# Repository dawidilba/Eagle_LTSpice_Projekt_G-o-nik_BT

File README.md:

## Eagle & LTSpice project - Przenosny głośnik bluetooth (schemat, wraz z symalacjami i PCB)

Projekt zrealizowany na przedmiot "Projektowanie Urządzeń Eletktronicznych" podczas 6 semestru studiów. W repozytorium znajdują się pliki źródłowe (wraz z potrzebnymi bibliotekami) do schematu i projektu płytki PCB (Program Eagle), a także symulacji (LTSpice). Dodatkowo zamieszczam szczegółową dokumentacje zrealizowanego projektu.

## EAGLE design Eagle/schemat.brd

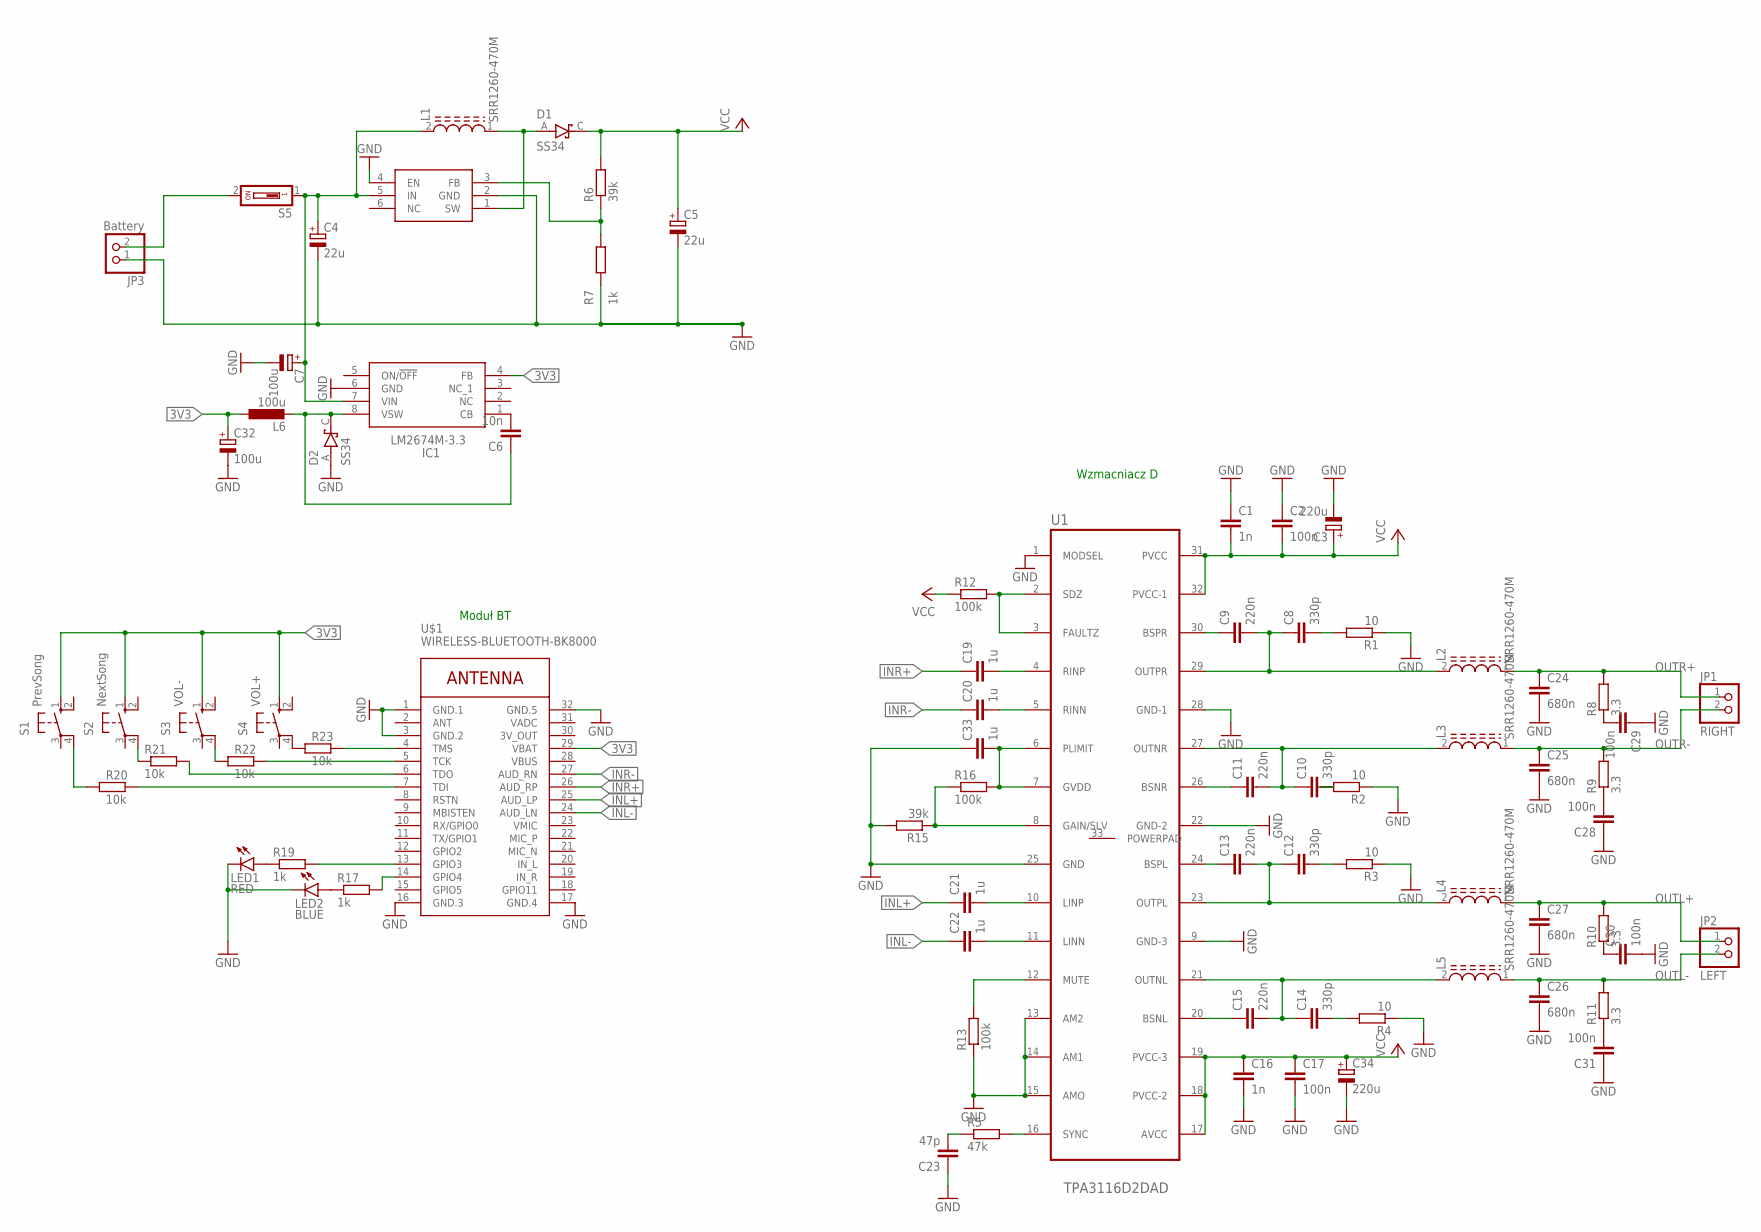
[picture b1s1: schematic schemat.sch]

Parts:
C1, C16: 1n; C0805
C2, C17, C28, C29, C30, C31: 100n; C0805
C3: 220u; 140CLH-0810
C4, C5: 22u; PANASONIC_D
C6: 10n; C0805
C7, C32: 100u; PANASONIC_D
C8, C10, C12, C14: 330p; C0805
C9, C11, C13, C15: 220n; C0805
C19, C20, C21, C22, C33: 1u; C0603
C23: 47p; C0603
C24, C25, C26, C27: 680n; C1206
C34: 220u; PANASONIC_D
D1, D2: SS34; DIOM7959X265N
IC1: LM2674M-3.3; SOIC127P600X175-8N
JP1: RIGHT; 1X02
JP2: LEFT; 1X02
JP3: Battery; 1X02
L1, L2, L3, L4, L5: SRR1260-470M; INDP125125X600N
L6: 100u; L1812
LED1: RED; CHIP-LED0805
LED2: BLUE; CHIP-LED0805
R1, R2, R3, R4: 10; R0805
R5: 47k; R0603
R6, R15: 39k; R0805
R7, R17, R19: 1k; R0805
R8, R9, R10, R11: 3.3; R0603
R12: 100k; R0603
R13, R16: 100k; R0805
R20, R21, R22, R23: 10k; R0805
S1: PrevSong; B3F-10XX
S2: NextSong; B3F-10XX
S3: VOL-; B3F-10XX
S4: VOL+; B3F-10XX
S5: DS01; DS-01
U1: TPA3116D2DAD; SOP65P810X120-33N
U2: MT3608; SOT95P280X145-6N
U$1: WIRELESS-BLUETOOTH-BK8000

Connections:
3V3: C32.+, IC1.4 (FB), L6.1, S1.1 (S), S2.1 (S), S3.1 (S), S4.1 (S), U$1.29 (VBAT)
3V_OUT: U$1.30 (3V_OUT)
BAT+: C4.+, C7.+, IC1.7 (VIN), L1.2, S5.1, U2.5 (IN)
BAT-: C4.-, C5.-, JP3.1, R7.1, U2.2 (GND)
GND: C1.1, C2.1, C3.-, C7.-, C16.2, C17.2, C23.1, C24.2, C25.2, C26.2, C27.2, C28.1, C29.1, C30.2, C31.1, C32.-, C33.1, C34.-, D2.A, IC1.6 (GND), LED1.C, LED2.C, R1.1, R2.1, R3.1, R4.1, R13.1, R15.2, U1.1 (MODSEL), U1.9 (GND-3), U1.13 (AM2), U1.14 (AM1), U1.15 (AMO), U1.22 (GND-2), U1.25 (GND), U1.28 (GND-1), U2.4 (EN), U$1.1 (GND.1), U$1.3 (GND.2), U$1.16 (GND.3), U$1.17 (GND.4), U$1.32 (GND.5)
INL+: C21.1, U$1.25 (AUD_LP)
INL-: C22.1, U$1.24 (AUD_LN)
INR+: C19.1, U$1.26 (AUD_RP)
INR-: C20.1, U$1.27 (AUD_RN)
unnamed: D1.A, L1.1, U2.1 (SW)
unnamed: C9.1, U1.30 (BSPR)
unnamed: C8.1, C9.2, L2.2, U1.29 (OUTPR)
unnamed: C12.1, C13.2, L4.2, U1.23 (OUTPL)
unnamed: C8.2, R1.2
unnamed: C11.1, U1.26 (BSNR)
unnamed: C10.1, C11.2, L3.2, U1.27 (OUTNR)
unnamed: C10.2, R2.2
unnamed: C13.1, U1.24 (BSPL)
unnamed: C15.1, U1.20 (BSNL)
unnamed: C12.2, R3.2
unnamed: C14.2, R4.2
unnamed: C6.1, D2.C (K), IC1.8 (VSW), L6.2
unnamed: R6.1, R7.2, U2.3 (FB)
unnamed: C19.2, U1.4 (RINP)
unnamed: C14.1, C15.2, L5.2, U1.21 (OUTNL)
unnamed: C20.2, U1.5 (RINN)
unnamed: C21.2, U1.10 (LINP)
unnamed: C22.2, U1.11 (LINN)
unnamed: C23.2, R5.1
unnamed: R5.2, U1.16 (SYNC)
unnamed: R22.1, S3.4 (P1)
unnamed: LED2.A, R17.1
unnamed: LED1.A, R19.1
unnamed: R17.2, U$1.14 (GPIO4)
unnamed: C28.2, R9.1
unnamed: C29.2, R8.1
unnamed: C30.1, R10.1
unnamed: C31.2, R11.1
unnamed: R12.2, U1.2 (SDZ), U1.3 (FAULTZ)
unnamed: R13.2, U1.12 (MUTE)
unnamed: C33.2, R16.2, U1.6 (PLIMIT), U1.7 (GVDD)
unnamed: R19.2, U$1.13 (GPIO3)
unnamed: R15.1, R16.1, U1.8 (GAIN/SLV)
unnamed: C6.2, IC1.1 (CB)
unnamed: R21.1, S2.4 (P1)
unnamed: R20.2, U$1.7 (TDI)
unnamed: R21.2, U$1.6 (TDO)
unnamed: R20.1, S1.4 (P1)
unnamed: R23.1, S4.4 (P1)
unnamed: JP3.2, S5.2
unnamed: R22.2, U$1.5 (TCK)
unnamed: R23.2, U$1.4 (TMS)
OUTL+: C27.1, JP2.1, L4.1, R10.2
OUTL-: C26.1, JP2.2, L5.1, R11.2
OUTR+: C24.1, JP1.1, L2.1, R8.2
OUTR-: C25.1, JP1.2, L3.1, R9.2
VADC: U$1.31 (VADC)
VCC: C1.2, C2.2, C3.+, C5.+, C16.1, C17.1, C34.+, D1.C (K), R6.2, R12.1, U1.17 (AVCC), U1.18 (PVCC-2), U1.19 (PVCC-3), U1.31 (PVCC), U1.32 (PVCC-1)

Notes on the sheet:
Moduł BT
Wzmacniacz D

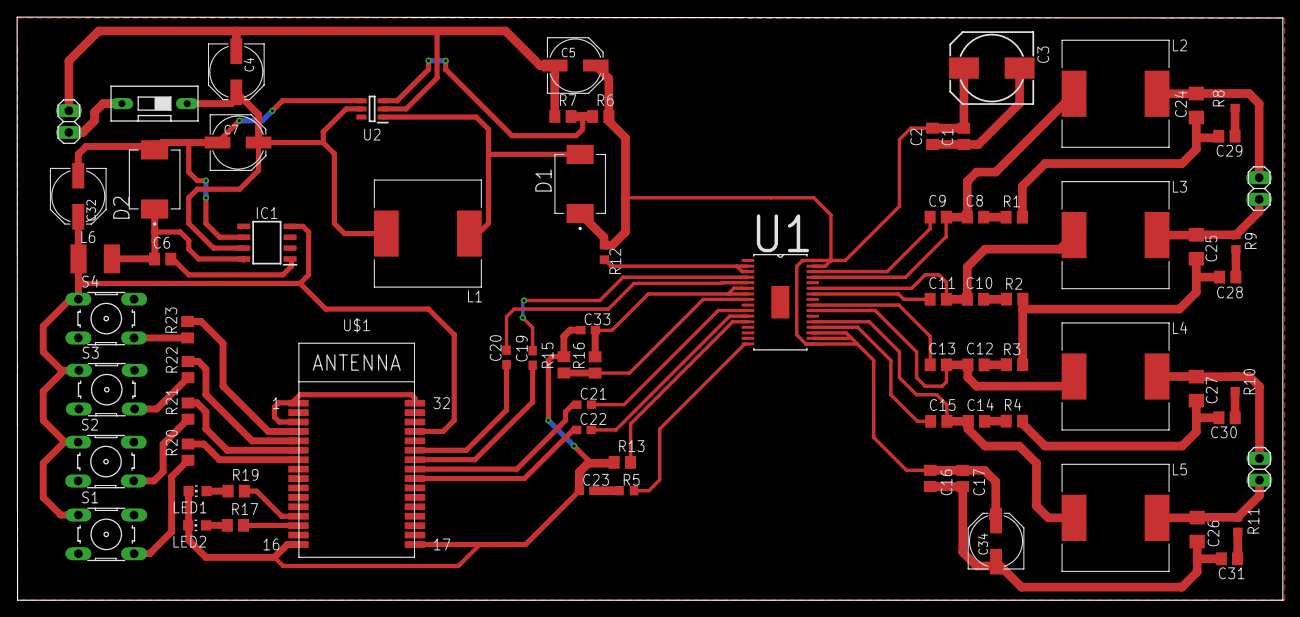
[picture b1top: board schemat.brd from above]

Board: 2 copper layers, 147.8 x 68.1 mm, 76 parts (0 on the bottom side), 56 nets.

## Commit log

2020-08-01 final version

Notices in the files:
parts and their libraries:
diy-modules: Released under the Creative Commons Attribution 4.0 International License: http://creativecommons.org/licenses/by/4.0
